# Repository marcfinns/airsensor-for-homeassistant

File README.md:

# AirSensor

A multi-room air quality monitor built around ESPHome and Home Assistant. Each unit sits flush on the wall like a light switch — mains powered, fully self-contained, nothing to charge or manage. Built on the ESP32-C6, it is hardware-ready for Matter, making it future-proof as smart home standards evolve.

---

## What it measures

Each unit reports the following to Home Assistant in real time:

| Sensor | Measurements |
|--------|-------------|
| **Sensirion SEN55** | PM1.0, PM2.5, PM4.0, PM10 · VOC Index · NOx Index · Temperature · Humidity |
| **Sensirion SCD4x** | CO2 (ppm) · Temperature · Humidity |
| **Infineon DPS310** *(optional)* | Barometric pressure · Temperature |

The DPS310 pressure sensor is fitted on one unit only and is entirely optional — the PCB and firmware support it but work fine without it.

---

## Display

Each unit has a **GC9A01A 240×240 round TFT** (SPI), sourced from AliExpress:

The display shows:
- **Time and date** (synced from Home Assistant)
- **CO2, humidity, PM2.5, VOC** values in the four quadrants
- A **5-segment AQI bar** reflecting the worst pollutant level across all sensors, colour-coded from green (Excellent) to red (Very Poor)
- A large **status word** (EXCELLENT / GOOD / FAIR / POOR / VERY POOR) at the centre
- An **animated fan graphic** as the background (see below)

The XIAO's built-in RGB LED *(optional)* breathes in the AQI colour — green through red depending on air quality — visible from across the room without looking at the display. It can be enabled or disabled from Home Assistant and the state persists across reboots.

---

## Animated fan

A **Fan Speed** entity (Off / Low / High) is exposed in Home Assistant. Selecting Low or High drives an animated three-blade fan spinning in the background of the display — slow and blue-purple at Low, faster and brighter purple at High. It is purely decorative and does not control any physical hardware. The selected speed persists across reboots.

---

## Hardware

| Component | Role |
|-----------|------|
| Seeed XIAO ESP32-C3 | MCU — different GPIO layout, otherwise identical firmware |
| Seeed XIAO ESP32-C6 | MCU — preferred variant; Wi-Fi 6, Matter-capable radio |
| Sensirion SEN55 | Particulate matter + VOC + NOx + T/RH |
| Sensirion SCD4x | CO2 + T/RH |
| Infineon DPS310 breakout | Barometric pressure *(optional)* |
| GC9A01A 240×240 round TFT | Round display (AliExpress) |
| Kradex Z123_W | Enclosure — standard wall-mount junction box |

The ESP32-C6 is the preferred variant. Its Wi-Fi 6 and IEEE 802.15.4 radio make it hardware-ready for Matter once ESPHome's Matter support matures. The C3 lacks the necessary radio and cannot support Matter.

---

## PCB

A single custom PCB designed in KiCad houses the MCU, sensors, and display connector inside the Kradex enclosure.

Custom KiCad libraries (symbols, footprints, and 3D models) are kept under `lib/` and referenced with portable `${KIPRJMOD}`-relative paths so the project opens correctly on any machine.

---

## Home Assistant integration

Each unit exposes the following entities:

- **Sensors** — all measured values listed above
- **Fan Speed** — select (Off / Low / High) to control the display animation
- **Status LED** — switch to enable or disable the breathing LED
- **Display Backlight** — light entity with brightness control
- **Restart** — button to reboot the device OTA

---

## MCU variants

| | ESP32-C3 | ESP32-C6 |
|-|----------|----------|
| Wi-Fi | 802.11 b/g/n | 802.11 b/g/n/ax (Wi-Fi 6) |
| BLE | 5.0 | 5.3 |
| Matter (future) | No — hardware limitation | Yes — IEEE 802.15.4 radio |
| GPIO | Different pinout | Reference pinout |

Two reference templates are provided — `ESPHome_config/AirSensor-C3.yaml` and `AirSensor-C6.yaml` — covering both variants.

---

## Repository structure

```
AirSensor/
├── ESPHome_config/
│   ├── AirSensor-C3.yaml          # Reference template (ESP32-C3)
│   ├── AirSensor-C6.yaml          # Reference template (ESP32-C6)
│   ├── airsensor_aqi_helpers.h    # Shared AQI logic (C++)
│   ├── secrets.yaml               # Empty secrets template
│   └── private/                   # Real deployment configs (gitignored)
├── kicad/
│   └── AirSensor_display/         # KiCad project (schematic + PCB)
├── lib/
│   ├── symbols/                   # Custom KiCad symbols
│   ├── footprints/                # Custom KiCad footprints
│   └── 3d/                        # 3D models for KiCad
├── mech/                          # Enclosure and module STEP files
└── docs/
    └── Data sheets/               # Component datasheets
```

---

## Getting started

1. Copy `ESPHome_config/AirSensor-C3.yaml` or `AirSensor-C6.yaml` to `ESPHome_config/private/<unit-name>.yaml`
2. Fill in `ESPHome_config/private/secrets.yaml` (Wi-Fi credentials, API key, OTA password)
3. Search for `← CONFIGURE` markers in the YAML and update each one (device name, floor label, etc.)
4. Remove the DPS310 sensor block if the pressure sensor is not fitted
5. Flash via ESPHome: `esphome run private/<unit-name>.yaml`

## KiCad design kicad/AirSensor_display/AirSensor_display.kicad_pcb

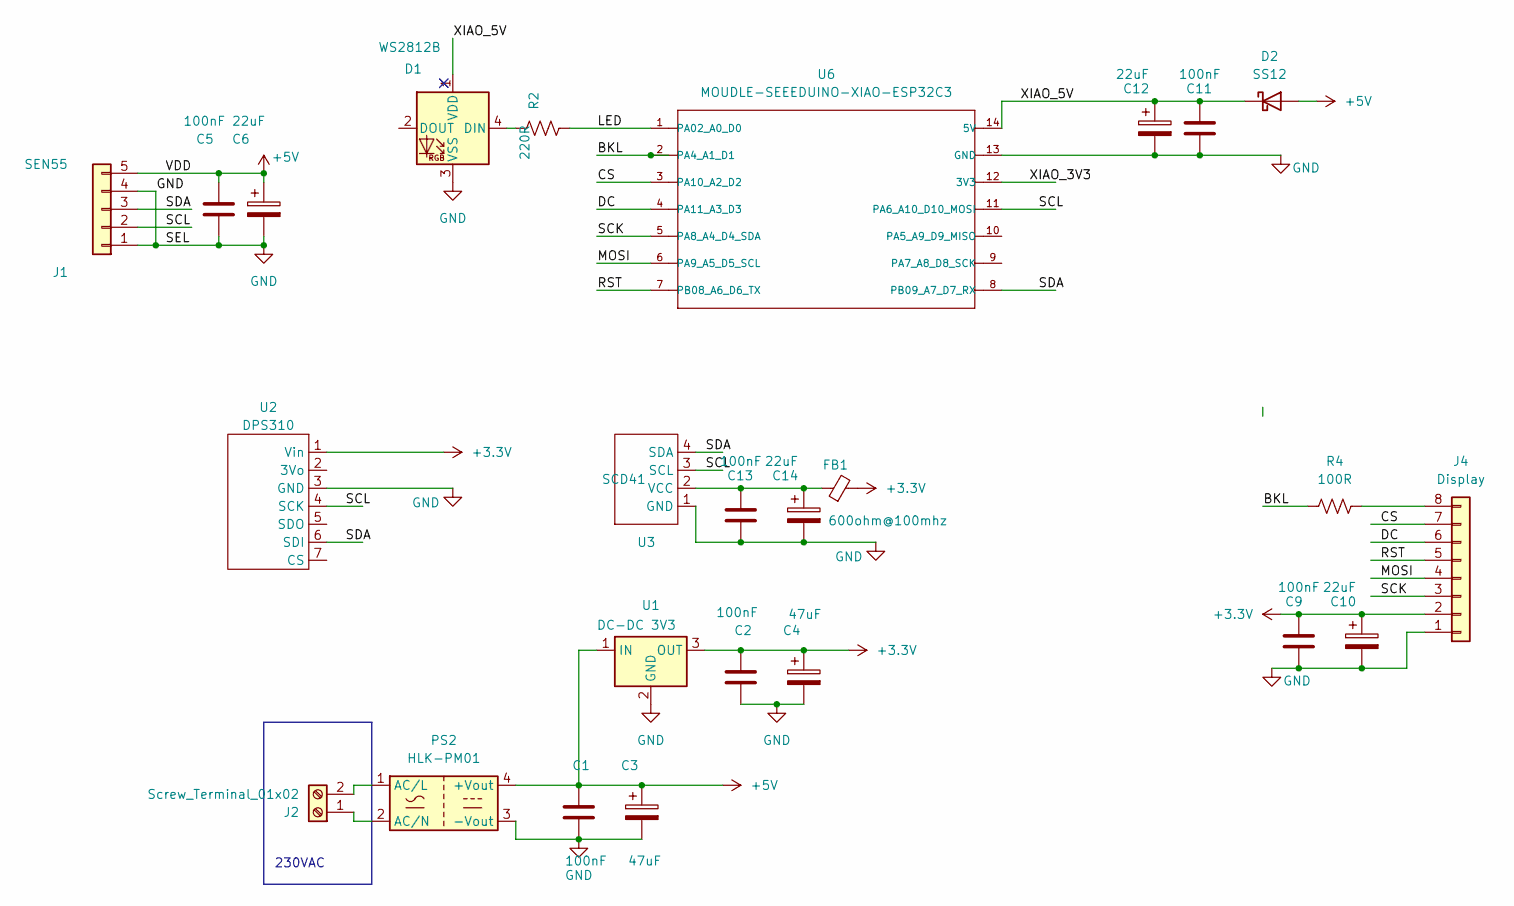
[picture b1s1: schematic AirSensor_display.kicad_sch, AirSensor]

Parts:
C1, C2, C5, C9, C11, C13: 100nF; C_0805_2012Metric_Pad1.18x1.45mm_HandSolder
C3, C4: 47uF; C_0805_2012Metric_Pad1.18x1.45mm_HandSolder
C6, C10, C12, C14: 22uF; C_0805_2012Metric_Pad1.18x1.45mm_HandSolder
D1: WS2812B; LED_WS2812B_PLCC4_5.0x5.0mm_P3.2mm
D2: SS12; D_SMA
FB1: 600ohm@100mhz; L_0805_2012Metric
J1: SEN55; JST_XH_B5B-XH-A_1x05_P2.50mm_Vertical
J2: Screw_Terminal_01x02; TerminalBlock_Phoenix_MKDS-1,5-2-5.08_1x02_P5.08mm_Horizont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
J4: Display; JST_XH_B8B-XH-AM_1x08_P2.50mm_Vertical
PS2: HLK-PM01; Converter_ACDC_Hi-Link_HLK-PMxx
R2: 220R; LED_0805_2012Metric_Pad1.15x1.40mm_HandSolder
R4: 100R; LED_0805_2012Metric_Pad1.15x1.40mm_HandSolder
U1: DC-DC 3V3; Converter_DCDC_Murata_OKI-78SR_Horizontal
U2: DPS310; DPS310_BREAKOUT
U3: SCD41; SCD41_BREAKOUT_1x4_2.54
U6: MOUDLE-SEEEDUINO-XIAO-ESP32C3; MOUDLE14P-SMD-2.54-21X17.8MM_PINONLY

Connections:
+3.3V: C2.1, C4.1, C9.1, C10.1, FB1.2, J4.2, U1.3 (OUT), U2.1 (Vin)
+5V: C1.1, C3.1, C5.1, C6.1, D2.2 (A), J1.5, PS2.4 (+Vout), U1.1 (IN)
/BKL: R4.2, U6.2 (PA4_A1_D1)
/CS: J4.7, U6.3 (PA10_A2_D2)
/DC: J4.6, U6.4 (PA11_A3_D3)
/LED: R2.1, U6.1 (PA02_A0_D0)
/MOSI: J4.4, U6.6 (PA9_A5_D5_SCL)
/RST: J4.5, U6.7 (PB08_A6_D6_TX)
/SCK: J4.3, U6.5 (PA8_A4_D4_SDA)
/SCL: J1.2, U2.4 (SCK), U3.3 (SCL), U6.11 (PA6_A10_D10_MOSI)
/SDA: J1.3, U2.6 (SDI), U3.4 (SDA), U6.8 (PB09_A7_D7_RX)
/XIAO_3V3: U6.12 (3V3)
/XIAO_5V: C11.1, C12.1, D1.1 (VDD), D2.1 (K), U6.14 (5V)
GND: C1.2, C2.2, C3.2, C4.2, C5.2, C6.2, C9.2, C10.2, C11.2, C12.2, C13.2, C14.2, D1.3 (VSS), J1.1, J1.4, J4.1, PS2.3 (-Vout), U1.2 (GND), U2.3 (GND), U3.1 (GND), U6.13 (GND)
unnamed: D1.4 (DIN), R2.2
unnamed: J2.1, PS2.2 (AC/N)
unnamed: J2.2, PS2.1 (AC/L)
unnamed: J4.8, R4.1
unnamed: C13.1, C14.1, FB1.1, U3.2 (VCC)

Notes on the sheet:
230VAC

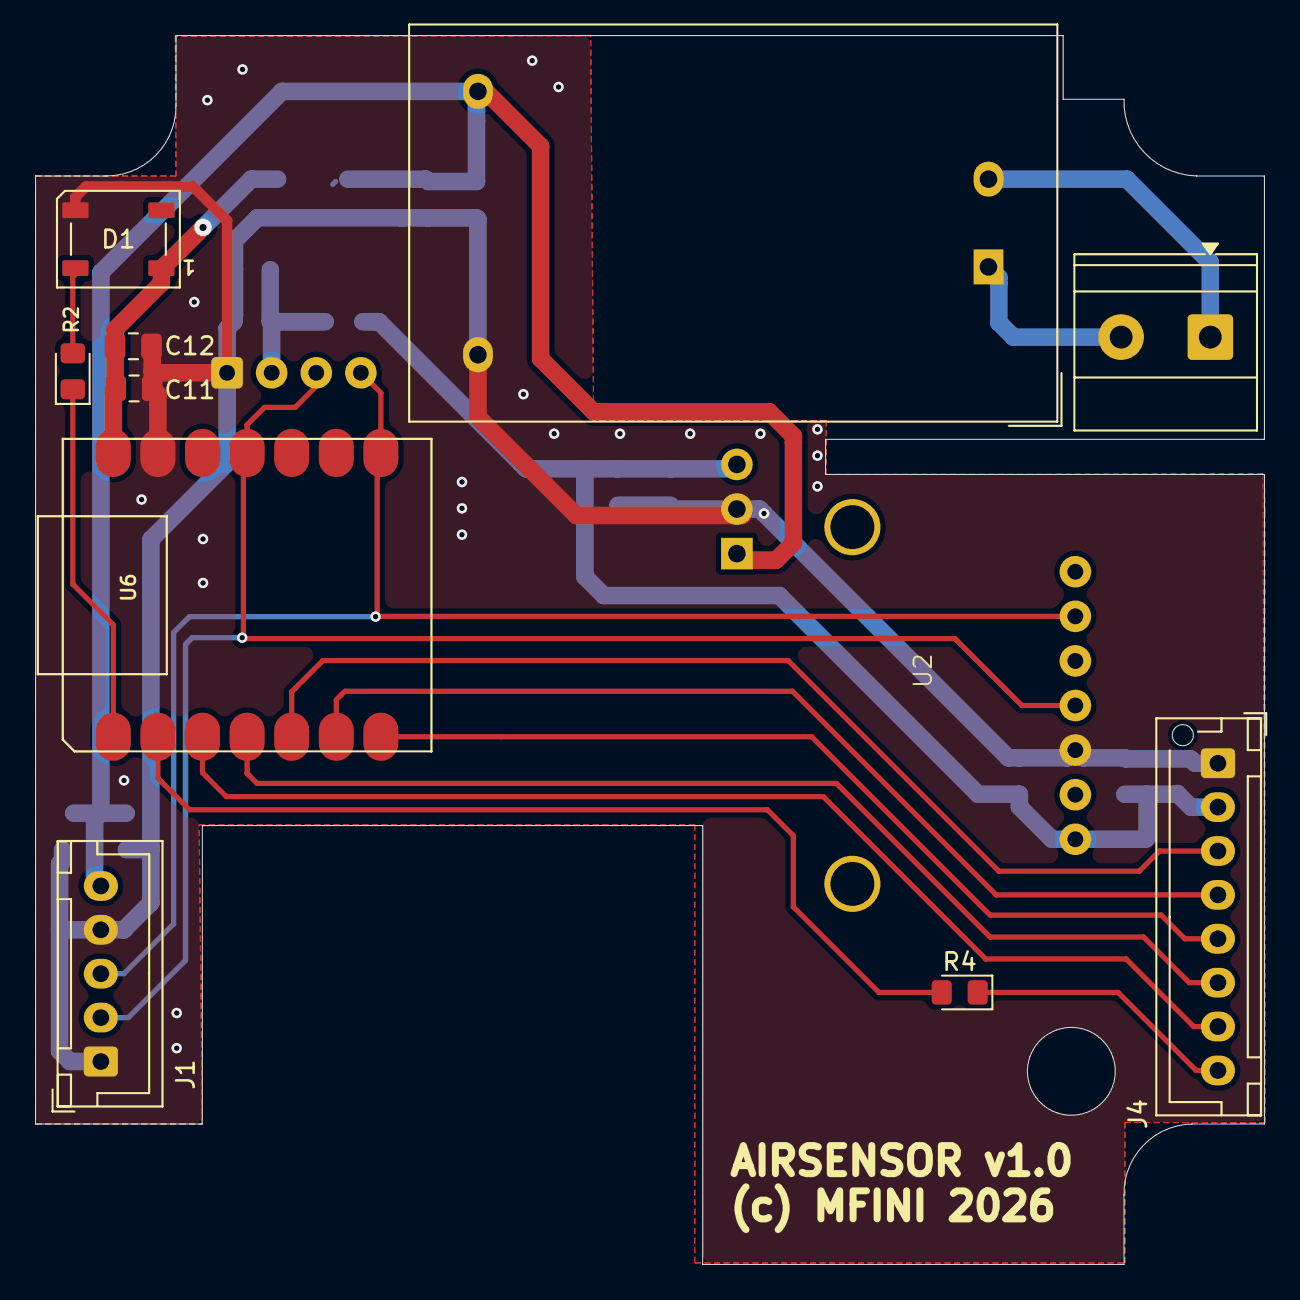
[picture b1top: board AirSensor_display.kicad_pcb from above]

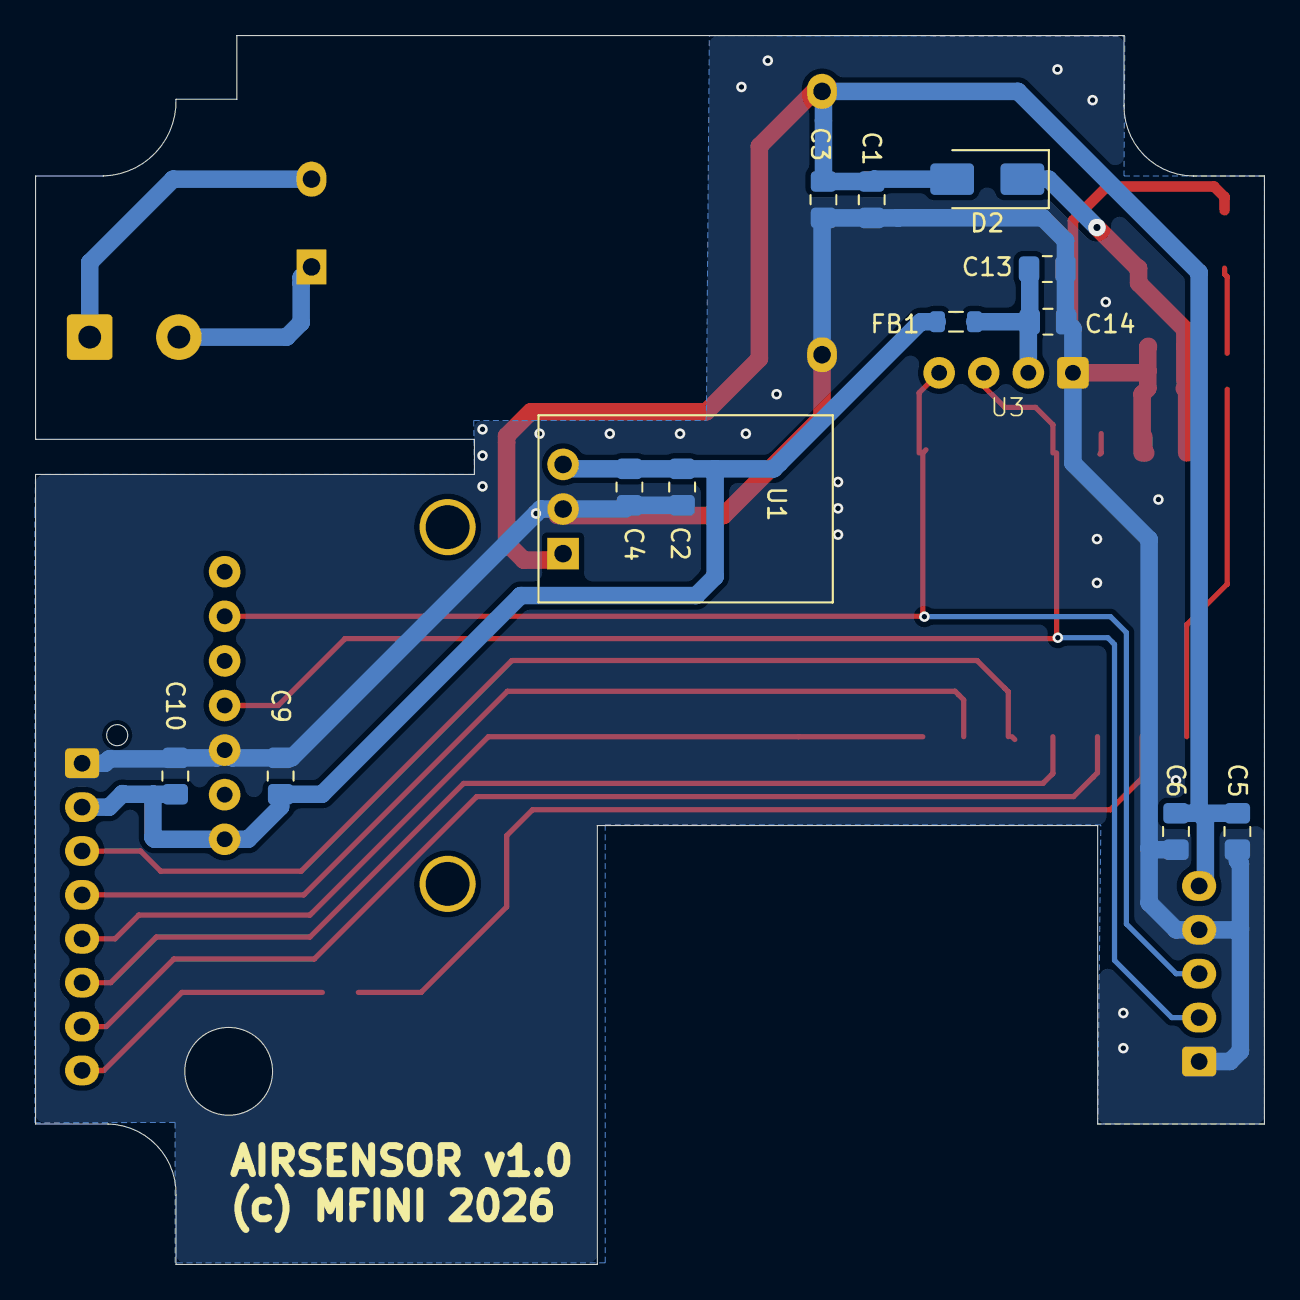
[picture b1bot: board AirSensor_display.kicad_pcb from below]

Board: 2 copper layers, 70.0 x 70.0 mm, 25 parts (14 on the bottom side), 18 nets.

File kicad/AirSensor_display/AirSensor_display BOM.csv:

"Reference","Qty","Value","DNP","Exclude from BOM","Exclude from Board","Footprint","Datasheet"
"C1,C2,C5,C9,C11,C13","6","100nF","","","","Capacitor_SMD:C_0805_2012Metric_Pad1.18x1.45mm_HandSolder","~"
"C3,C4","2","47uF","","","","Capacitor_SMD:C_0805_2012Metric_Pad1.18x1.45mm_HandSolder","~"
"C6,C10,C12,C14","4","22uF","","","","Capacitor_SMD:C_0805_2012Metric_Pad1.18x1.45mm_HandSolder","~"
"D1","1","WS2812B","","","","LED_SMD:LED_WS2812B_PLCC4_5.0x5.0mm_P3.2mm","https://cdn-shop.adafruit.com/datasheets/WS2812B.pdf"
"D2","1","SS12","","","","Diode_SMD:D_SMA","https://www.vishay.com/docs/88746/ss12.pdf"
"FB1","1","600ohm@100mhz","","","","Inductor_SMD:L_0805_2012Metric","~"
"J1","1","SEN55","","","","Connector_JST:JST_XH_B5B-XH-A_1x05_P2.50mm_Vertical","~"
"J2","1","Screw_Terminal_01x02","","","","TerminalBlock_Phoenix:TerminalBlock_Phoenix_MKDS-1,5-2-5.08_1x02_P5.08mm_Horizontal","~"
"J4","1","Display","","","","Connector_JST:JST_XH_B8B-XH-AM_1x08_P2.50mm_Vertical","~"
"PS2","1","HLK-PM01","","","","Converter_ACDC:Converter_ACDC_Hi-Link_HLK-PMxx","https://h.hlktech.com/download/ACDC%E7%94%B5%E6%BA%90%E6%A8%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"
"R2","1","220R","","","","LED_SMD:LED_0805_2012Metric_Pad1.15x1.40mm_HandSolder","~"
"R4","1","100R","","","","LED_SMD:LED_0805_2012Metric_Pad1.15x1.40mm_HandSolder","~"
"U1","1","DC-DC 3V3","","","","Converter_DCDC:Converter_DCDC_Murata_OKI-78SR_Horizontal","https://power.murata.com/data/power/oki-78sr.pdf"
"U2","1","DPS310","","","","AirSensor_footprints:DPS310_BREAKOUT",""
"U3","1","SCD41","","","","AirSensor_footprints:SCD41_BREAKOUT_1x4_2.54",""
"U6","1","MOUDLE-SEEEDUINO-XIAO-ESP32C3","","","","xiao ESP32C3_PCB:MOUDLE14P-SMD-2.54-21X17.8MM_PINONLY",""
